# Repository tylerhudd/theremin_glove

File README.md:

# Theremin Glove
The Theremin Glove is a theremin inspired electronic instrument. Like the theremin, it is played with hand movements and gestures in the air. In electronics terms, it is a digitally controlled analog synthesizer and a wireless glove controller.
 
This project was started for the Johns Hopkins Whiting School of Engineering *Embedded Systems Lab* course in September 2019 and the working prototype should be demonstrated in December 2019. This course is an Electrical and Computer Engineerng graduate level capstone class that emulates the design process from requirement definitions to project demonstration.

I came up with the concept for this project as a way to combine areas of my engineering interests, which include:
* Analog circuit design
* Digital circuit design
* Firmware design (in this case, it's C programming for the ATMega328P)
* PCB design

## Features
* Pitch control - raising and lowering hand raises and lowers the frequency generated by the analog synthesizer
* Definable pitch range - the pitch range is set by first defining where the lowest note exists (i.e. place hand at the bottom of range) and press a button to start range recording. Then raise hand to where the highest note is and press a button to save. This is required because hand placement will be detected by an accelerometer which doesn't measure absolute height.
* Tone control - tilting hand in and out sweeps the resonant frequencies of the analog filters in the synthesizer
* Volume control - opening and closing hand raises and lowers the volume

## System
### Glove
* XBee3 wireless RF transceiver - transmits sensor data to digital analog synthesizer controller
* ATMega328P microcontroller - reads the sensor data and pushes to the XBee3 over SPI
* I2C interface to 6DoF sensor
* ADC interface to bend sensor
* USB-UART interface to ATMega328P and XBee3 for debug
* AVR SPI ISP header for ATMega328P programming
* Battery powered
* USB re-chargeable

### Digital Analog Synthesizer Controller
* XBee3 wireless RF transceiver - receives sensor data from glove
* ATMega328P microcontroller - interprets sensor data and calculates controls to analog synthesizer
* I2C interface to 4-channel DAC and IO expander
* USB-UART interface to ATMega328P and XBee3 for debug
* AVR SPI ISP header for ATMega328P programming

### Analog Synthesizer
* 4-channel DAC - provides control voltages to analog circuis
* I2C IO expander - provides a greater number of control signals
* VCO - generates square, triangle, and sine waveforms
* VCF - variable low pass, band pass, and high pass filters
* VCA - variable volume amplifier
* Analog muxes to select waveforms and filtering
* Audio output

### Power Board
* Input 12VAC (2A max)
* Ouput :
 * +3.3V DC (1.5A max) for digital circuits
 * +/-12V DC (1.5A max each) for analog circuits

### Block Diagram

## Tools Used
* Atmel Studio - for ATMega328P C firmware development and programming
* KiCAD - for schematic capture and PCB design
* LTSpice - for analog and power simulations
* PuTTY - for serial console
* Github - for configuration management and project documentation

## Resources
* http://musicfromouterspace.com/
* https://oshpark.com/

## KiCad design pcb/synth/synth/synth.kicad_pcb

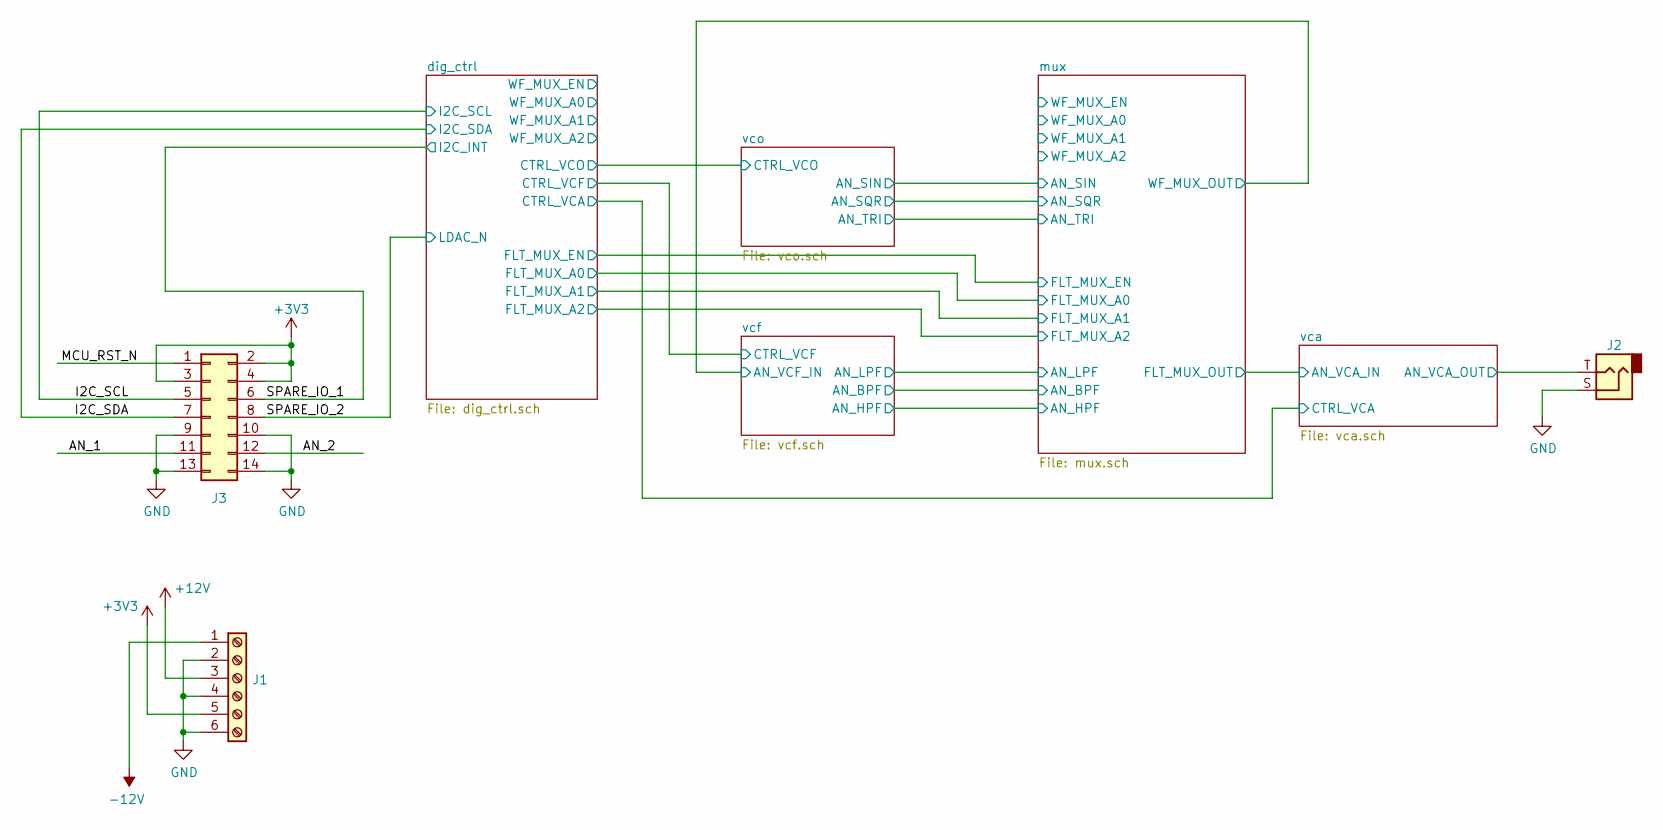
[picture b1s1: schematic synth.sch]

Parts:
J1: Screw_Terminal_01x06; TerminalBlock_bornier-6_P5.08mm
J2: AudioJack2; PinHeader_1x02_P2.54mm_Vertical
J3: Conn_02x07_Odd_Even; PinHeader_2x07_P2.54mm_Vertical

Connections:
+12V: J1.3; also elsewhere on the board
/AN_1: J3.11; also elsewhere on the board
/AN_2: J3.12; also elsewhere on the board
/I2C_SCL: J3.6; also elsewhere on the board
/I2C_SDA: J3.8; also elsewhere on the board
/SPARE_IO_1: J3.5; also elsewhere on the board
/SPARE_IO_2: J3.7; also elsewhere on the board
/vca/AN_VCA_OUT: J2.T; also elsewhere on the board
GND: J1.2, J1.4, J1.6, J2.S, J3.9, J3.10, J3.13, J3.14; also elsewhere on the board

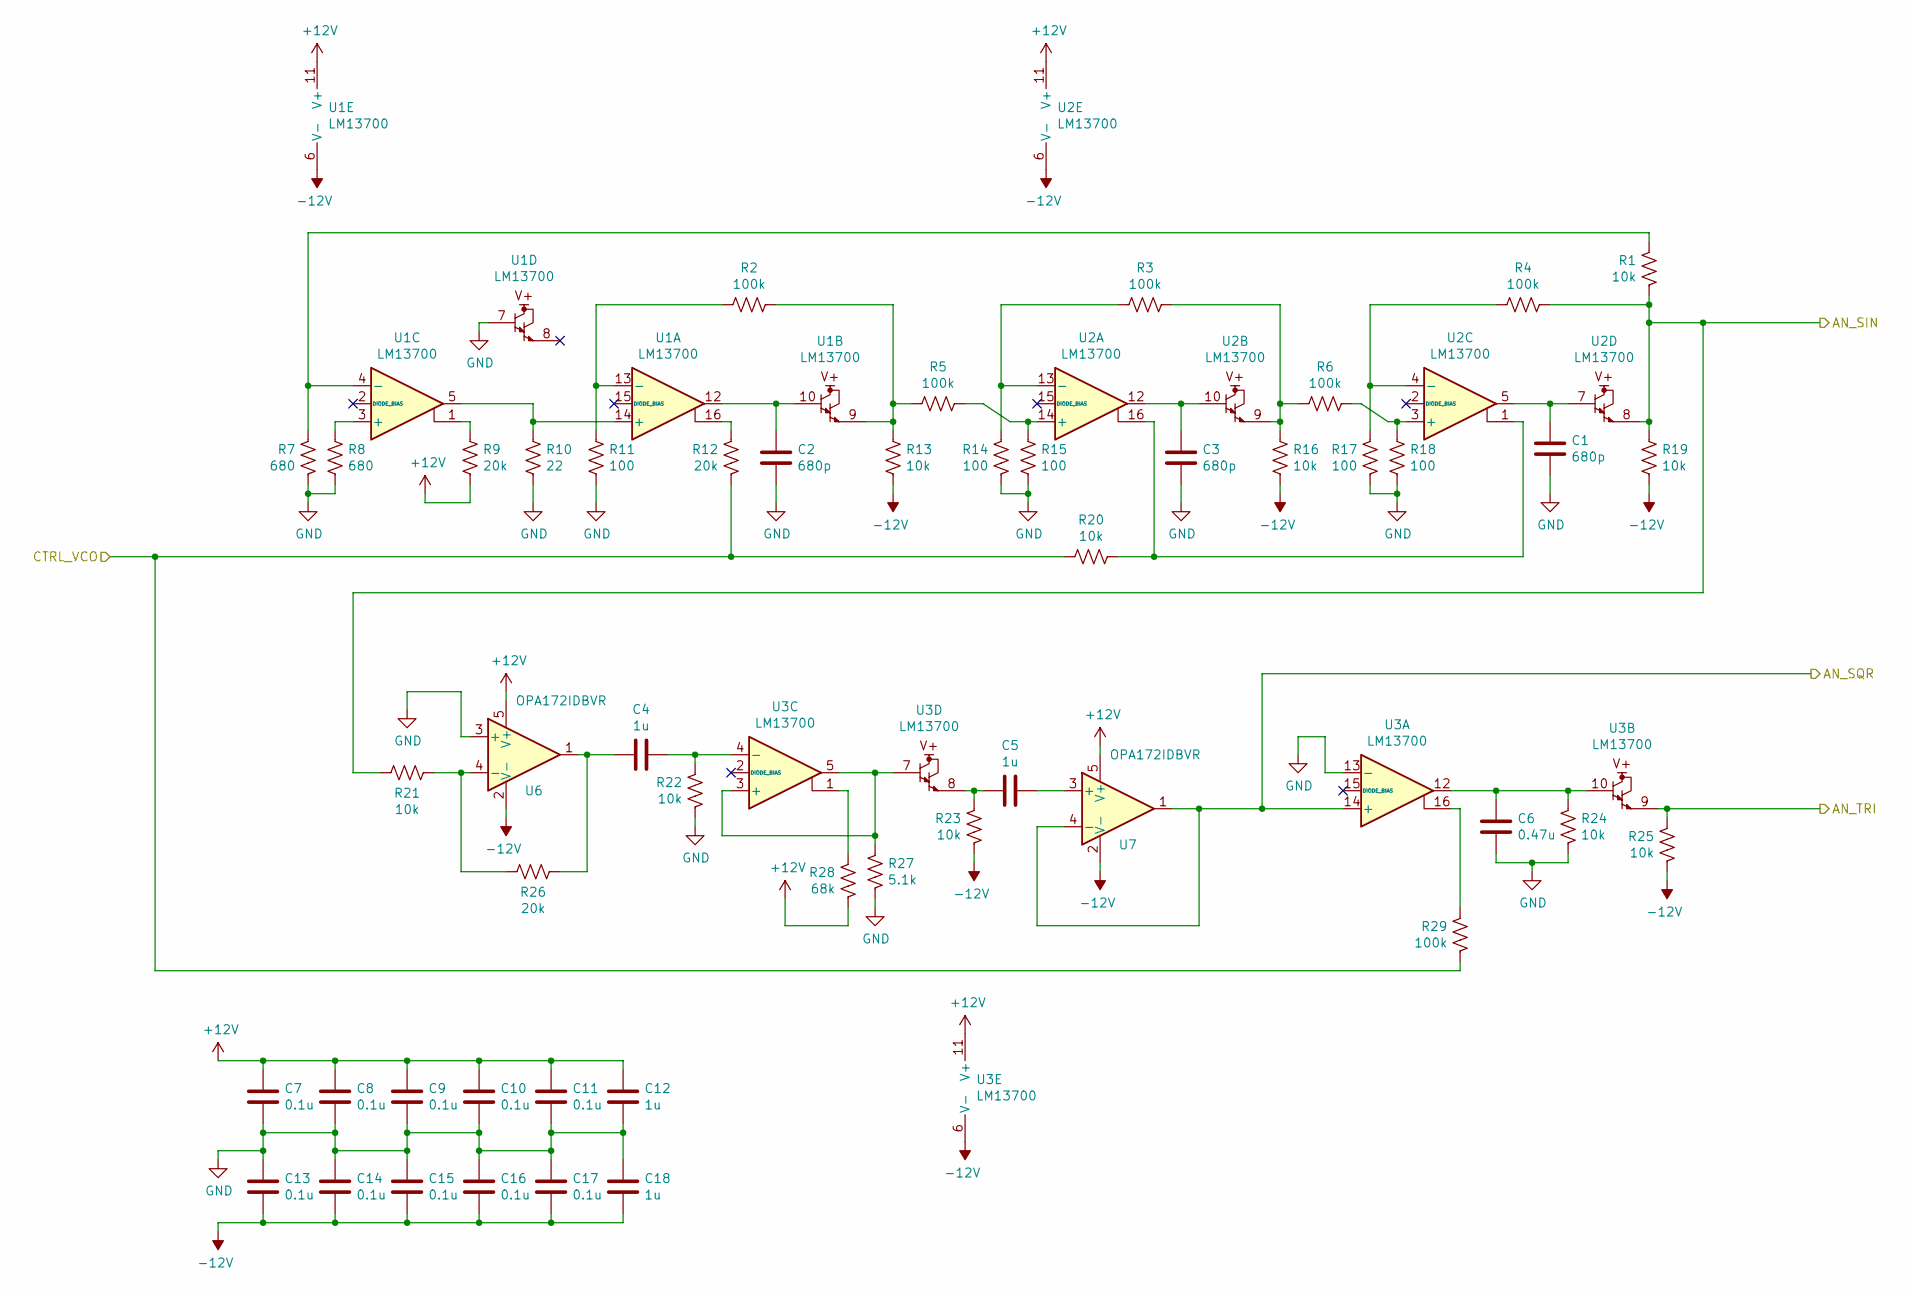
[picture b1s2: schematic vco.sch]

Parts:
C1, C2, C3: 680p; C_0603_1608Metric_Pad1.05x0.95mm_HandSolder
C4, C5, C12, C18: 1u; C_0603_1608Metric_Pad1.05x0.95mm_HandSolder
C6: 0.47u; C_0603_1608Metric_Pad1.05x0.95mm_HandSolder
C7, C8, C9, C10, C11, C13, C14, C15, C16, C17: 0.1u; C_0603_1608Metric_Pad1.05x0.95mm_HandSolder
R1, R13, R16, R19, R20, R21, R22, R23, R24, R25: 10k; R_0603_1608Metric_Pad1.05x0.95mm_HandSolder
R2, R3, R4, R5, R6, R29: 100k; R_0603_1608Metric_Pad1.05x0.95mm_HandSolder
R7, R8: 680; R_0603_1608Metric_Pad1.05x0.95mm_HandSolder
R9, R12, R26: 20k; R_0603_1608Metric_Pad1.05x0.95mm_HandSolder
R10: 22; R_0603_1608Metric_Pad1.05x0.95mm_HandSolder
R11, R14, R15, R17, R18: 100; R_0603_1608Metric_Pad1.05x0.95mm_HandSolder
R27: 5.1k; R_0603_1608Metric_Pad1.05x0.95mm_HandSolder
R28: 68k; R_0603_1608Metric_Pad1.05x0.95mm_HandSolder
U1, U2, U3: LM13700; SOIC-16_3.9x9.9mm_P1.27mm
U6, U7: OPA172IDBVR; SOT-23-5

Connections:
+12V: C7.1, C8.1, C9.1, C10.1, C11.1, C12.1, R9.1, R28.1, U1.11 (V+), U2.11 (V+), U3.11 (V+), U6.5 (V+), U7.5 (V+); also elsewhere on the board
/dig_ctrl/CTRL_VCO: R12.1, R20.2, R29.1; also elsewhere on the board
/mux/AN_SIN: R1.1, R4.1, R19.2, R21.2, U2.8; also elsewhere on the board
/mux/AN_SQR: U3.14 (+), U7.1, U7.4 (-); also elsewhere on the board
/mux/AN_TRI: R25.2, U3.9; also elsewhere on the board
GND: C1.2, C2.2, C3.2, C6.2, C7.2, C8.2, C9.2, C10.2, C11.2, C12.2, C13.1, C14.1, C15.1, C16.1, C17.1, C18.1, R7.1, R8.1, R10.1, R11.1, R14.1, R15.1, R17.1, R18.1, R22.1, R24.1, R27.1, U1.7, U3.13 (-), U6.3 (+); also elsewhere on the board
unnamed: C1.1, U2.5, U2.7
unnamed: C2.1, U1.10, U1.12
unnamed: C3.1, U2.10, U2.12
unnamed: C4.1, R26.1, U6.1
unnamed: C4.2, R22.2, U3.4 (-)
unnamed: C5.1, R23.2, U3.8
unnamed: C5.2, U7.3 (+)
unnamed: C6.1, R24.2, U3.10, U3.12
unnamed: R1.2, R7.2, U1.4 (-)
unnamed: R8.2, U1.3 (+)
unnamed: R9.2, U1.1
unnamed: R10.2, U1.5, U1.14 (+)
unnamed: R2.2, R11.2, U1.13 (-)
unnamed: R12.2, U1.16
unnamed: R2.1, R5.2, R13.2, U1.9
unnamed: R3.2, R14.2, U2.13 (-)
unnamed: R5.1, R15.2, U2.14 (+)
unnamed: R3.1, R6.2, R16.2, U2.9
unnamed: R4.2, R17.2, U2.4 (-)
unnamed: R6.1, R18.2, U2.3 (+)
unnamed: R20.1, U2.1, U2.16
unnamed: R21.1, R26.2, U6.4 (-)
unnamed: R27.2, U3.3 (+), U3.5, U3.7
unnamed: R28.2, U3.1
unnamed: R29.2, U3.16

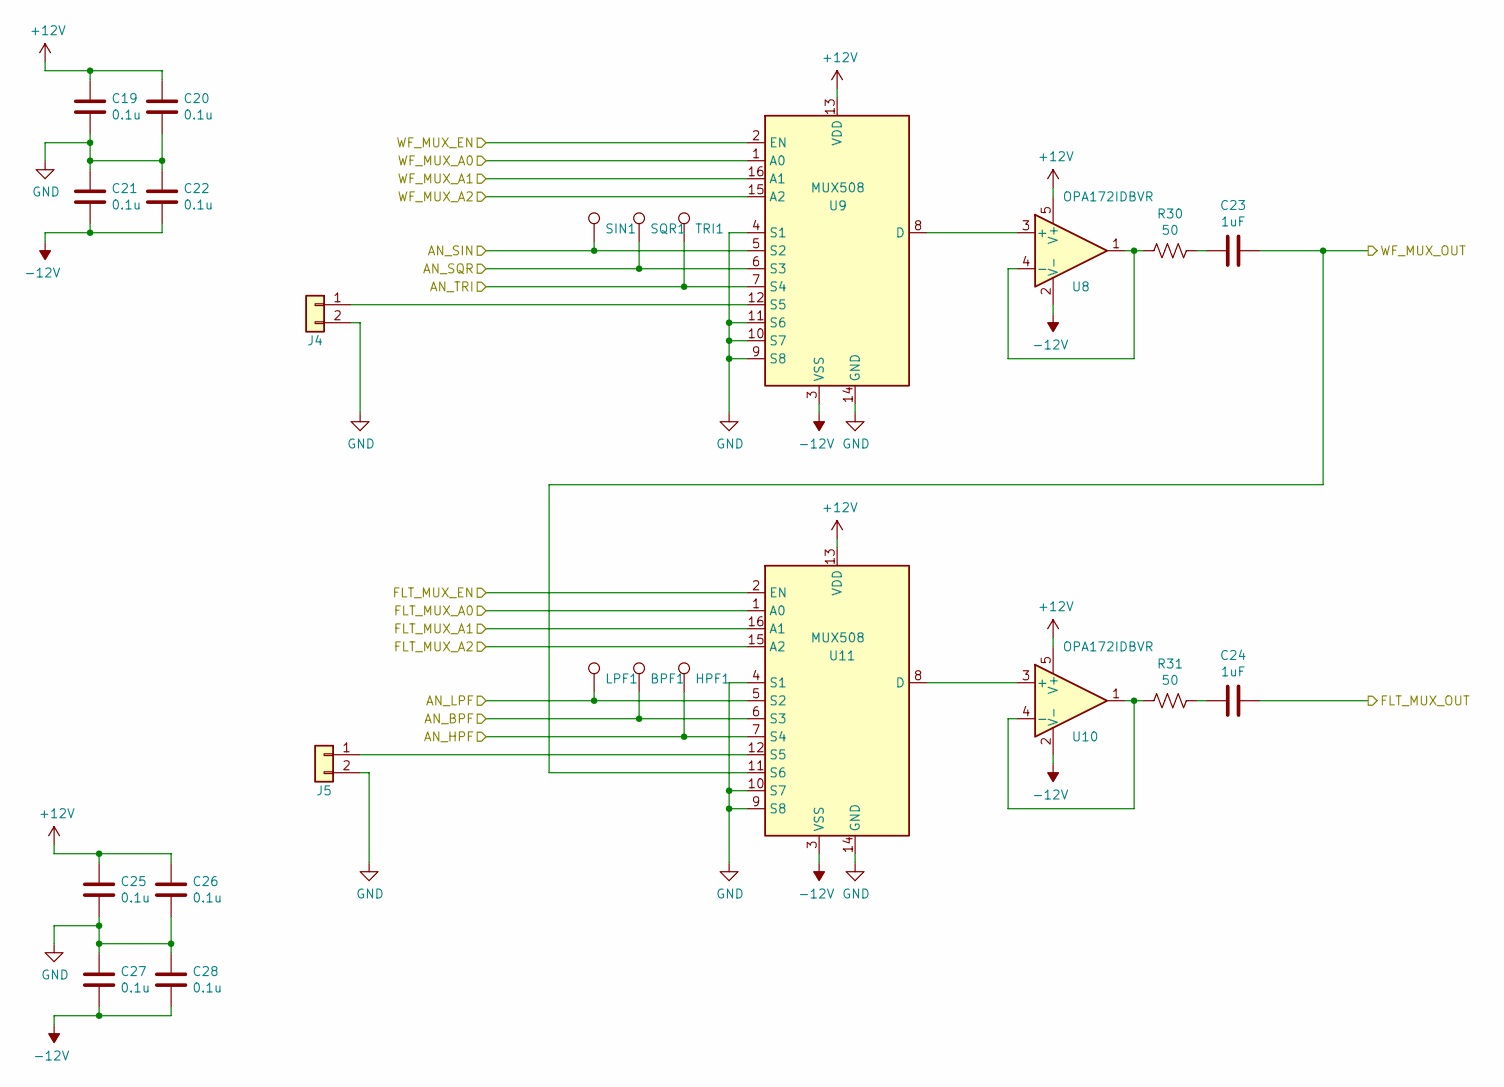
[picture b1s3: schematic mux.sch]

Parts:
BPF1: TestPoint; TestPoint_Pad_1.0x1.0mm
C19, C20, C21, C22, C25, C26, C27, C28: 0.1u; C_0603_1608Metric_Pad1.05x0.95mm_HandSolder
C23, C24: 1uF; C_0603_1608Metric_Pad1.05x0.95mm_HandSolder
HPF1: TestPoint; TestPoint_Pad_1.0x1.0mm
J4, J5: Conn_01x02; PinHeader_1x02_P2.54mm_Vertical
LPF1: TestPoint; TestPoint_Pad_1.0x1.0mm
R30, R31: 50; R_0603_1608Metric_Pad1.05x0.95mm_HandSolder
SIN1: TestPoint; TestPoint_Pad_1.0x1.0mm
SQR1: TestPoint; TestPoint_Pad_1.0x1.0mm
TRI1: TestPoint; TestPoint_Pad_1.0x1.0mm
U8, U10: OPA172IDBVR; SOT-23-5
U9, U11: MUX508; SOIC-16_3.9x9.9mm_P1.27mm

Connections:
+12V: C19.1, C20.1, C25.1, C26.1, U8.5 (V+), U9.13 (VDD), U10.5 (V+), U11.13 (VDD); also elsewhere on the board
/dig_ctrl/FLT_MUX_A0: U11.1 (A0); also elsewhere on the board
/dig_ctrl/FLT_MUX_A1: U11.16 (A1); also elsewhere on the board
/dig_ctrl/FLT_MUX_A2: U11.15 (A2); also elsewhere on the board
/dig_ctrl/FLT_MUX_EN: U11.2 (EN); also elsewhere on the board
/dig_ctrl/WF_MUX_A0: U9.1 (A0); also elsewhere on the board
/dig_ctrl/WF_MUX_A1: U9.16 (A1); also elsewhere on the board
/dig_ctrl/WF_MUX_A2: U9.15 (A2); also elsewhere on the board
/dig_ctrl/WF_MUX_EN: U9.2 (EN); also elsewhere on the board
/mux/AN_BPF: BPF1.1, U11.6 (S3); also elsewhere on the board
/mux/AN_HPF: HPF1.1, U11.7 (S4); also elsewhere on the board
/mux/AN_LPF: LPF1.1, U11.5 (S2); also elsewhere on the board
/mux/AN_SIN: SIN1.1, U9.5 (S2); also elsewhere on the board
/mux/AN_SQR: SQR1.1, U9.6 (S3); also elsewhere on the board
/mux/AN_TRI: TRI1.1, U9.7 (S4); also elsewhere on the board
/vca/AN_VCA_IN: C24.2; also elsewhere on the board
/vcf/AN_VCF_IN: C23.2, U11.11 (S6); also elsewhere on the board
GND: C19.2, C20.2, C21.1, C22.1, C25.2, C26.2, C27.1, C28.1, J4.2, J5.2, U9.4 (S1), U9.9 (S8), U9.10 (S7), U9.11 (S6), U9.14 (GND), U11.4 (S1), U11.9 (S8), U11.10 (S7), U11.14 (GND); also elsewhere on the board
unnamed: C23.1, R30.1
unnamed: C24.1, R31.1
unnamed: J4.1, U9.12 (S5)
unnamed: J5.1, U11.12 (S5)
unnamed: R30.2, U8.1, U8.4 (-)
unnamed: R31.2, U10.1, U10.4 (-)
unnamed: U8.3 (+), U9.8 (D)
unnamed: U10.3 (+), U11.8 (D)

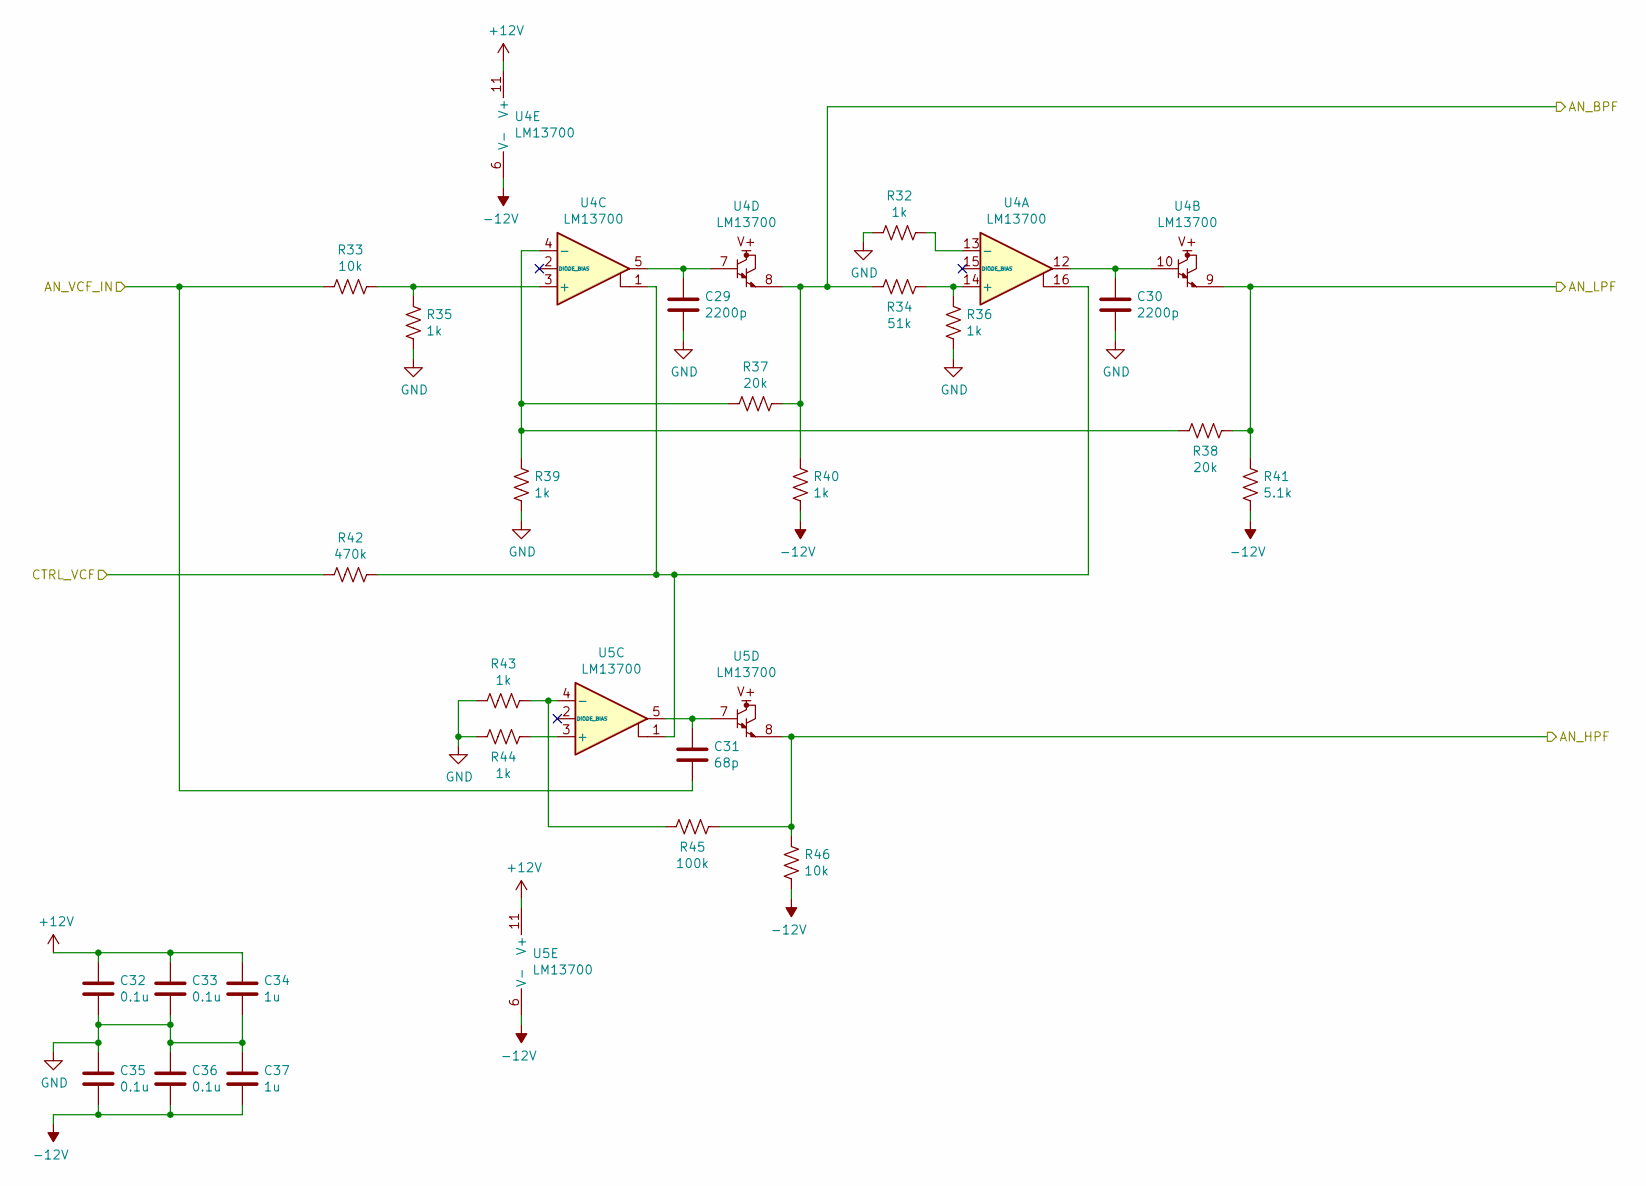
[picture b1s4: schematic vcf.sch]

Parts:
C29, C30: 2200p; C_0603_1608Metric_Pad1.05x0.95mm_HandSolder
C31: 68p; C_0603_1608Metric_Pad1.05x0.95mm_HandSolder
C32, C33, C35, C36: 0.1u; C_0603_1608Metric_Pad1.05x0.95mm_HandSolder
C34, C37: 1u; C_0603_1608Metric_Pad1.05x0.95mm_HandSolder
R32, R35, R36, R39, R40, R43, R44: 1k; R_0603_1608Metric_Pad1.05x0.95mm_HandSolder
R33, R46: 10k; R_0603_1608Metric_Pad1.05x0.95mm_HandSolder
R34: 51k; R_0603_1608Metric_Pad1.05x0.95mm_HandSolder
R37, R38: 20k; R_0603_1608Metric_Pad1.05x0.95mm_HandSolder
R41: 5.1k; R_0603_1608Metric_Pad1.05x0.95mm_HandSolder
R42: 470k; R_0603_1608Metric_Pad1.05x0.95mm_HandSolder
R45: 100k; R_0603_1608Metric_Pad1.05x0.95mm_HandSolder
U4, U5: LM13700; SOIC-16_3.9x9.9mm_P1.27mm

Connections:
+12V: C32.1, C33.1, C34.1, U4.11 (V+), U5.11 (V+); also elsewhere on the board
/dig_ctrl/CTRL_VCF: R42.2; also elsewhere on the board
/mux/AN_BPF: R34.2, R37.1, R40.1, U4.8; also elsewhere on the board
/mux/AN_HPF: R45.2, R46.1, U5.8; also elsewhere on the board
/mux/AN_LPF: R38.1, R41.1, U4.9; also elsewhere on the board
/vcf/AN_VCF_IN: C31.2, R33.2; also elsewhere on the board
GND: C29.2, C30.2, C32.2, C33.2, C34.2, C35.1, C36.1, C37.1, R32.2, R35.2, R36.2, R39.2, R43.1, R44.1; also elsewhere on the board
unnamed: C29.1, U4.5, U4.7
unnamed: C30.1, U4.10, U4.12
unnamed: C31.1, U5.5, U5.7
unnamed: R32.1, U4.13 (-)
unnamed: R33.1, R35.1, U4.3 (+)
unnamed: R34.1, R36.1, U4.14 (+)
unnamed: R37.2, R38.2, R39.1, U4.4 (-)
unnamed: R42.1, U4.1, U4.16, U5.1
unnamed: R43.2, R45.1, U5.4 (-)
unnamed: R44.2, U5.3 (+)

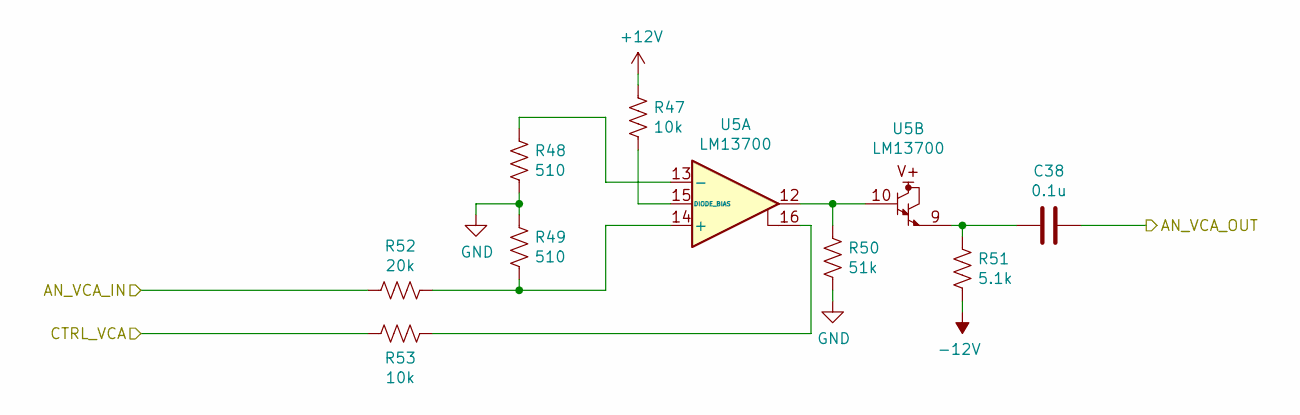
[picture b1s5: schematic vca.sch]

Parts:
C38: 0.1u; C_0603_1608Metric_Pad1.05x0.95mm_HandSolder
R47, R53: 10k; R_0603_1608Metric_Pad1.05x0.95mm_HandSolder
R48, R49: 510; R_0603_1608Metric_Pad1.05x0.95mm_HandSolder
R50: 51k; R_0603_1608Metric_Pad1.05x0.95mm_HandSolder
R51: 5.1k; R_0603_1608Metric_Pad1.05x0.95mm_HandSolder
R52: 20k; R_0603_1608Metric_Pad1.05x0.95mm_HandSolder
U5: LM13700; SOIC-16_3.9x9.9mm_P1.27mm

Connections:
+12V: R47.2; also elsewhere on the board
/dig_ctrl/CTRL_VCA: R53.2; also elsewhere on the board
/vca/AN_VCA_IN: R52.2; also elsewhere on the board
/vca/AN_VCA_OUT: C38.1; also elsewhere on the board
GND: R48.1, R49.2, R50.1; also elsewhere on the board
unnamed: C38.2, R51.2, U5.9
unnamed: R47.1, U5.15 (DIODE_BIAS)
unnamed: R48.2, U5.13 (-)
unnamed: R49.1, R52.1, U5.14 (+)
unnamed: R50.2, U5.10, U5.12
unnamed: R53.1, U5.16

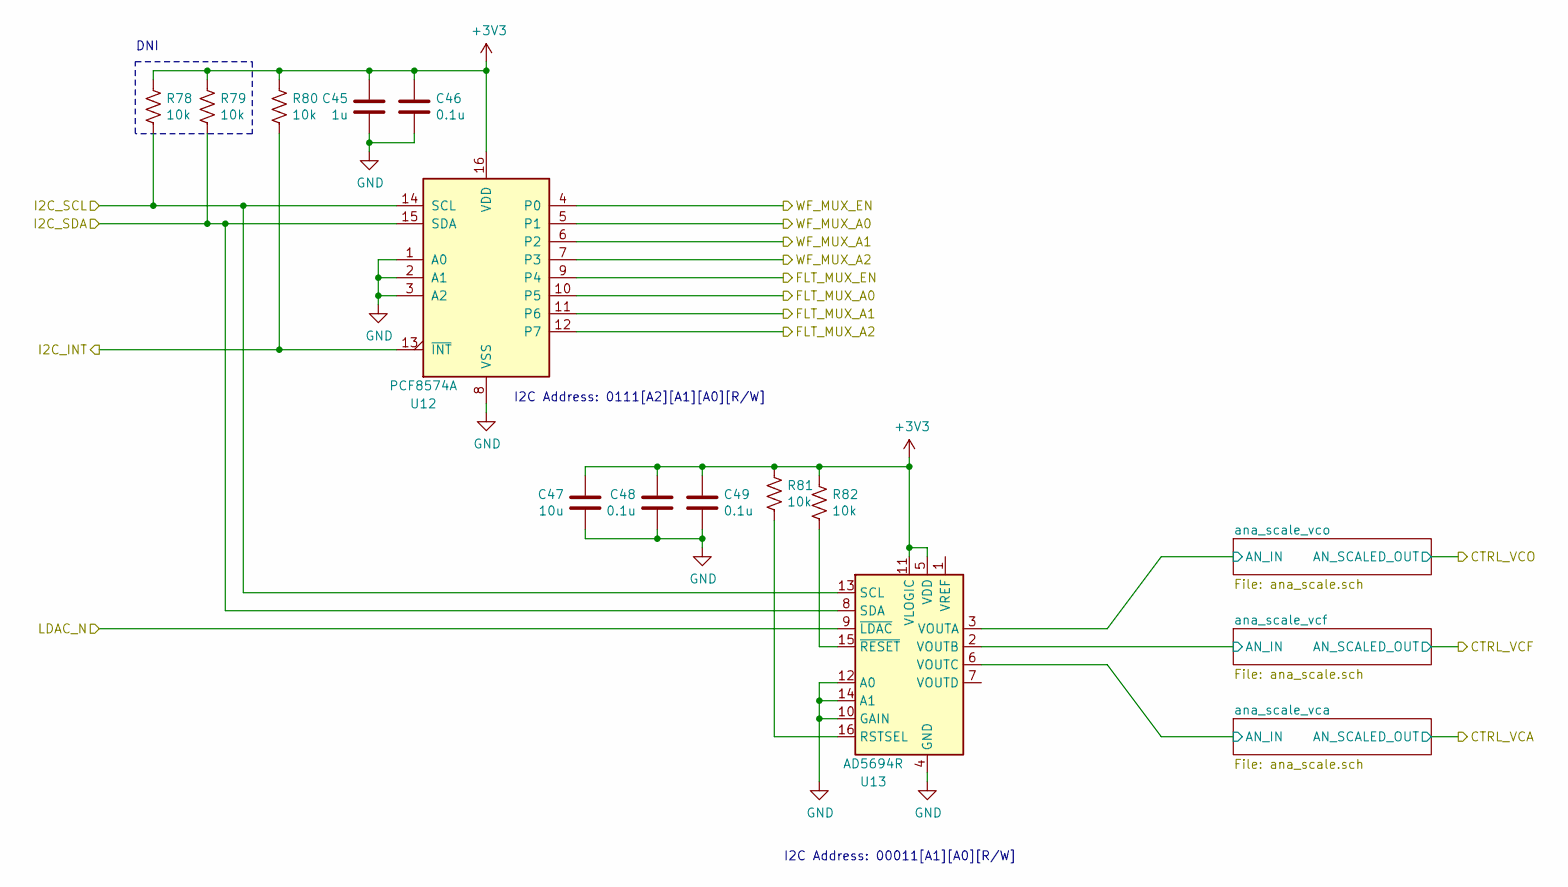
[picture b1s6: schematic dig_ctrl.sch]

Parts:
C45: 1u; C_0603_1608Metric_Pad1.05x0.95mm_HandSolder
C46, C48, C49: 0.1u; C_0603_1608Metric_Pad1.05x0.95mm_HandSolder
C47: 10u; C_0603_1608Metric_Pad1.05x0.95mm_HandSolder
R78, R79, R80, R81, R82: 10k; R_0603_1608Metric_Pad1.05x0.95mm_HandSolder
U12: PCF8574A; SOIC-16W-12_7.5x10.3mm_P1.27mm
U13: AD5694R; TSSOP-16_4.4x5mm_P0.65mm

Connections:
/I2C_SCL: R78.2, U12.14 (SCL), U13.13 (SCL); also elsewhere on the board
/I2C_SDA: R79.2, U12.15 (SDA), U13.8 (SDA); also elsewhere on the board
/SPARE_IO_1: R80.2, U12.13 (~INT~); also elsewhere on the board
/SPARE_IO_2: U13.9 (~LDAC); also elsewhere on the board
/dig_ctrl/FLT_MUX_A0: U12.10 (P5); also elsewhere on the board
/dig_ctrl/FLT_MUX_A1: U12.11 (P6); also elsewhere on the board
/dig_ctrl/FLT_MUX_A2: U12.12 (P7); also elsewhere on the board
/dig_ctrl/FLT_MUX_EN: U12.9 (P4); also elsewhere on the board
/dig_ctrl/WF_MUX_A0: U12.5 (P1); also elsewhere on the board
/dig_ctrl/WF_MUX_A1: U12.6 (P2); also elsewhere on the board
/dig_ctrl/WF_MUX_A2: U12.7 (P3); also elsewhere on the board
/dig_ctrl/WF_MUX_EN: U12.4 (P0); also elsewhere on the board
/dig_ctrl/ana_scale_vca/AN_IN: U13.6 (VOUTC); also elsewhere on the board
/dig_ctrl/ana_scale_vcf/AN_IN: U13.2 (VOUTB); also elsewhere on the board
/dig_ctrl/ana_scale_vco/AN_IN: U13.3 (VOUTA); also elsewhere on the board
GND: C45.2, C46.2, C47.2, C48.2, C49.2, U12.1 (A0), U12.2 (A1), U12.3 (A2), U12.8 (VSS), U13.4 (GND), U13.10 (GAIN), U13.12 (A0), U13.14 (A1); also elsewhere on the board
unnamed: R81.2, U13.16 (RSTSEL)
unnamed: R82.2, U13.15 (~RESET)
unnamed 101: U13.7 (VOUTD); also elsewhere on the board

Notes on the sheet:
I2C Address: 0111[A2][A1][A0][R/W]
I2C Address: 00011[A1][A0][R/W]
DNI

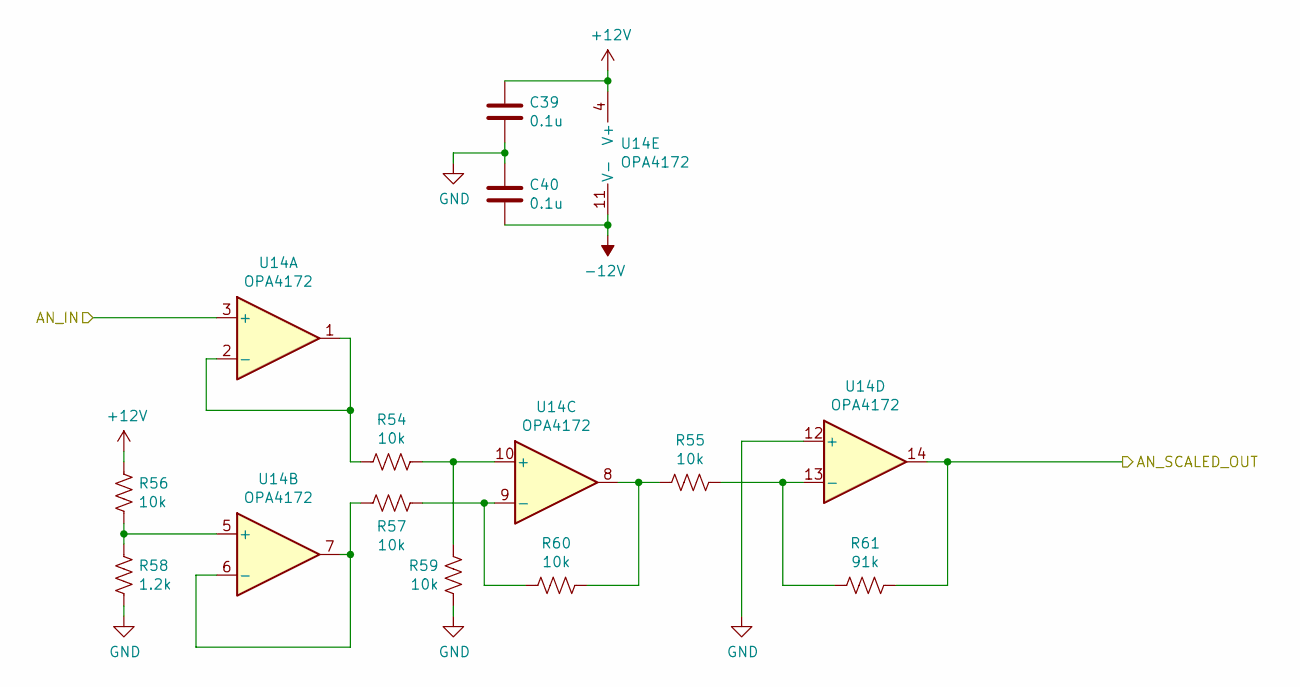
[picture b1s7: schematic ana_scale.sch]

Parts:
C39, C40: 0.1u; C_0603_1608Metric_Pad1.05x0.95mm_HandSolder
R54, R55, R56, R57, R59, R60: 10k; R_0603_1608Metric_Pad1.05x0.95mm_HandSolder
R58: 1.2k; R_0603_1608Metric_Pad1.05x0.95mm_HandSolder
R61: 91k; R_0603_1608Metric_Pad1.05x0.95mm_HandSolder
U14: OPA4172; SOIC-14_3.9x8.7mm_P1.27mm

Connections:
+12V: C39.1, R56.1, U14.4 (V+); also elsewhere on the board
/dig_ctrl/CTRL_VCO: R61.2, U14.14; also elsewhere on the board
/dig_ctrl/ana_scale_vco/AN_IN: U14.3 (+); also elsewhere on the board
GND: C39.2, C40.1, R58.2, R59.2, U14.12 (+); also elsewhere on the board
unnamed: R54.1, U14.1, U14.2 (-)
unnamed: R54.2, R59.1, U14.10 (+)
unnamed: R55.1, R60.2, U14.8
unnamed: R55.2, R61.1, U14.13 (-)
unnamed: R56.2, R58.1, U14.5 (+)
unnamed: R57.1, U14.6 (-), U14.7
unnamed: R57.2, R60.1, U14.9 (-)

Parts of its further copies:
C41, C42, C43, C44: 0.1u; C_0603_1608Metric_Pad1.05x0.95mm_HandSolder
R62, R63, R64, R65, R67, R68, R70, R71, R72, R73, R75, R76: 10k; R_0603_1608Metric_Pad1.05x0.95mm_HandSolder
R66, R74: 1.2k; R_0603_1608Metric_Pad1.05x0.95mm_HandSolder
U15, U16: OPA4172; SOIC-14_3.9x8.7mm_P1.27mm

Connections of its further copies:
+12V: C41.1, C43.1, R64.1, R72.1, U15.4 (V+), U16.4 (V+); also elsewhere on the board
/dig_ctrl/CTRL_VCA: U16.14; also elsewhere on the board
/dig_ctrl/CTRL_VCF: U15.14; also elsewhere on the board
/dig_ctrl/ana_scale_vca/AN_IN: U16.3 (+); also elsewhere on the board
/dig_ctrl/ana_scale_vcf/AN_IN: U15.3 (+); also elsewhere on the board
GND: C41.2, C42.1, C43.2, C44.1, R66.2, R67.2, R74.2, R75.2, U15.12 (+), U16.12 (+); also elsewhere on the board
unnamed: R62.1, U15.1, U15.2 (-)
unnamed: R62.2, R67.1, U15.10 (+)
unnamed: R63.1, R68.2, U15.8
unnamed 88: R63.2, U15.13 (-); also elsewhere on the board
unnamed: R64.2, R66.1, U15.5 (+)
unnamed: R65.1, U15.6 (-), U15.7
unnamed: R65.2, R68.1, U15.9 (-)
unnamed: R70.1, U16.1, U16.2 (-)
unnamed: R70.2, R75.1, U16.10 (+)
unnamed: R71.1, R76.2, U16.8
unnamed 95: R71.2, U16.13 (-); also elsewhere on the board
unnamed: R72.2, R74.1, U16.5 (+)
unnamed: R73.1, U16.6 (-), U16.7
unnamed: R73.2, R76.1, U16.9 (-)

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
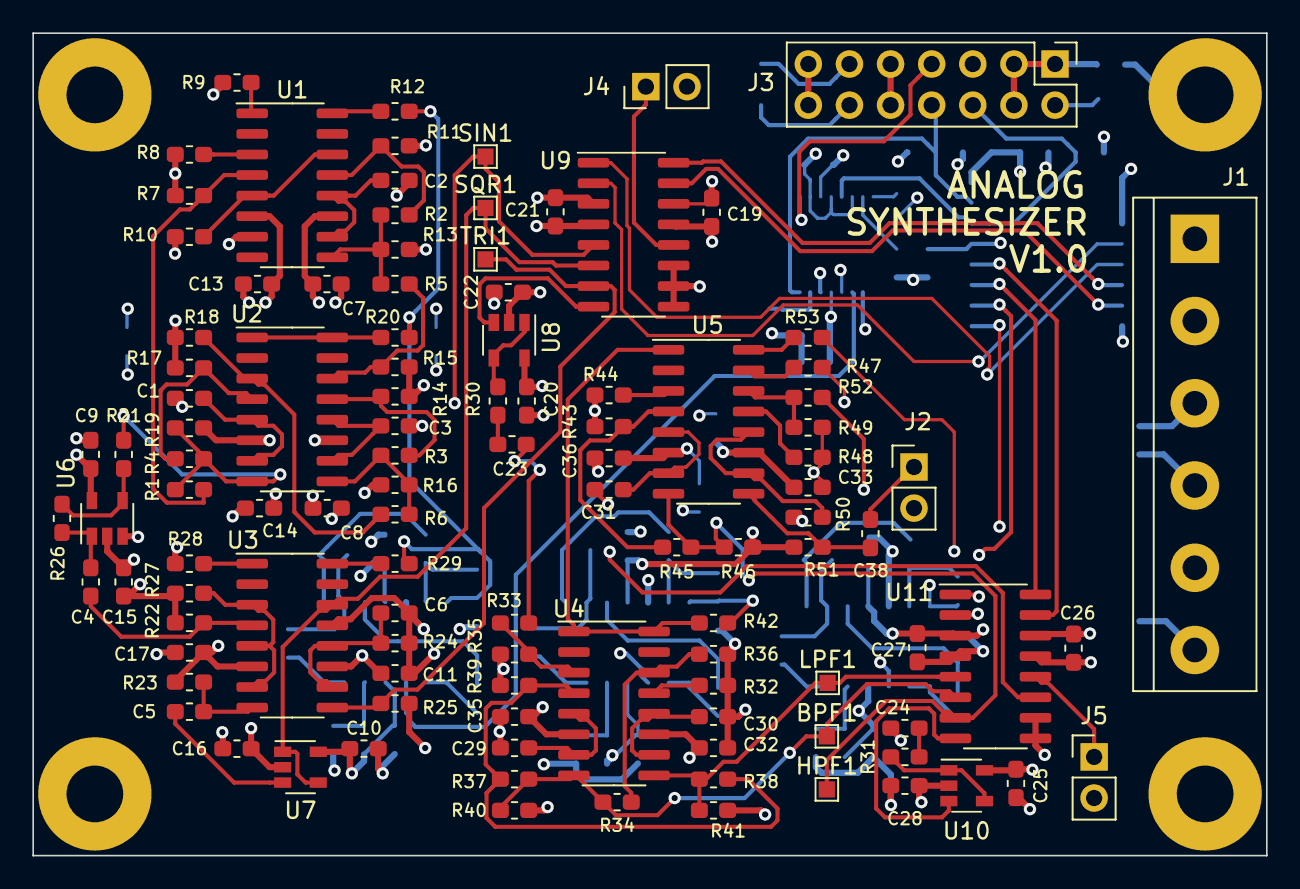
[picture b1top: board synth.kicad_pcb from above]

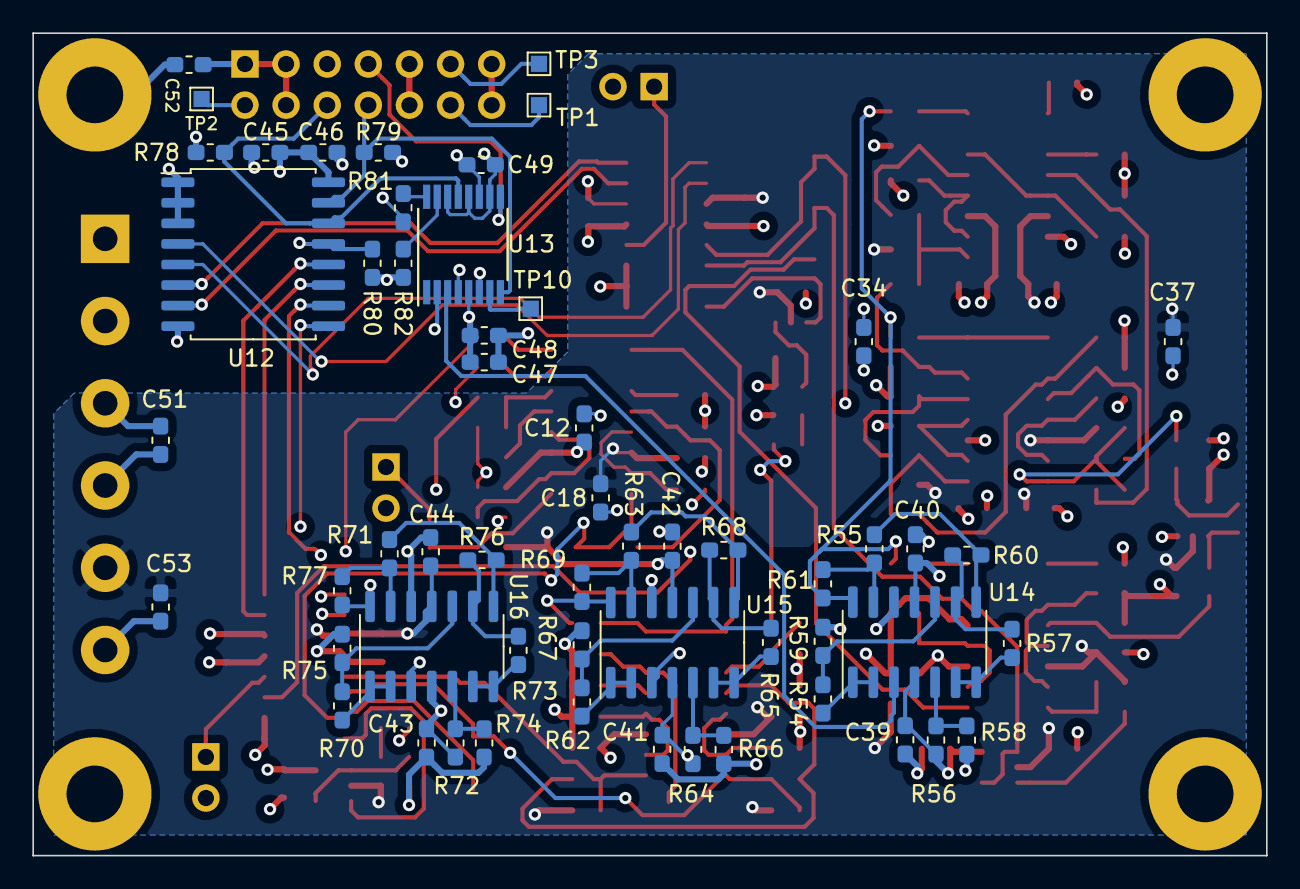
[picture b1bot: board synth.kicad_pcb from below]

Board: 4 copper layers, 76.2 x 50.8 mm, 165 parts (56 on the bottom side), 107 nets.

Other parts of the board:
C51, C52, C53: 10u; C_0603_1608Metric_Pad1.05x0.95mm_HandSolder
R69, R77: 10k; R_0603_1608Metric_Pad1.05x0.95mm_HandSolder
TP1, TP2, TP3, TP10: TestPoint; TestPoint_Pad_1.0x1.0mm

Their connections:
+12V: C51.1; also elsewhere on the board
/AN_1: TP3.1; also elsewhere on the board
/AN_2: TP1.1; also elsewhere on the board
/dig_ctrl/CTRL_VCA: R77.2; also elsewhere on the board
/dig_ctrl/CTRL_VCF: R69.2; also elsewhere on the board
GND: C51.2, C52.2, C53.1; also elsewhere on the board
unnamed 88: R69.1; also elsewhere on the board
unnamed 95: R77.1; also elsewhere on the board
unnamed 101: TP10.1; also elsewhere on the board

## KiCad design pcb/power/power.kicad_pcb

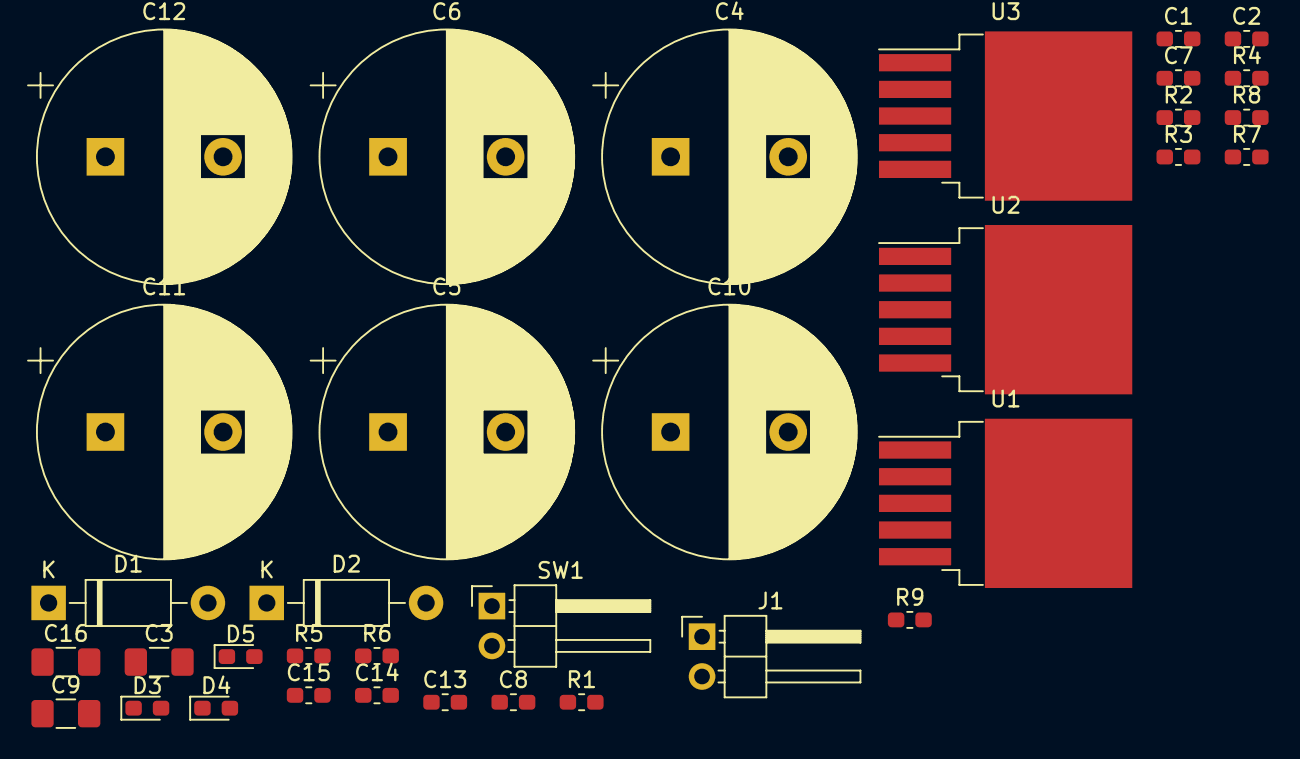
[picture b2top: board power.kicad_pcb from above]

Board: 2 copper layers, 35 parts (0 on the bottom side), 14 nets, no tracks yet.

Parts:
C1, C2, C7, C8, C13, C15: 1uF; C_0603_1608Metric_Pad1.05x0.95mm_HandSolder
C3, C9, C16: 10uF; C_1206_3216Metric_Pad1.42x1.75mm_HandSolder
C4, C5, C6, C10, C11, C12: 3300uF; CP_Radial_D16.0mm_P7.50mm
C14: 10nF; C_0603_1608Metric_Pad1.05x0.95mm_HandSolder
D1, D2: 1N4004; D_DO-41_SOD81_P10.16mm_Horizontal
D3, D4, D5: LED; LED_0603_1608Metric_Pad1.05x0.95mm_HandSolder
J1: Barrel_Jack; PinHeader_1x02_P2.54mm_Horizontal
R1: 330k; R_0603_1608Metric_Pad1.05x0.95mm_HandSolder
R2, R4, R6: 12.1k; R_0603_1608Metric_Pad1.05x0.95mm_HandSolder
R3: 1.2Meg; R_0603_1608Metric_Pad1.05x0.95mm_HandSolder
R5: 107K; R_0603_1608Metric_Pad1.05x0.95mm_HandSolder
R7: 330; R_0603_1608Metric_Pad1.05x0.95mm_HandSolder
R8, R9: 1k; R_0603_1608Metric_Pad1.05x0.95mm_HandSolder
SW1: SW_SPST; PinHeader_1x02_P2.54mm_Horizontal
U1, U2: LT3080xQ; TO-263-5_TabPin3
U3: LT3015Q; TO-263-5_TabPin3

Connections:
+3V3: C2.1, C3.1, D3.2, R2.1, U1.3
+12V: C8.1, C9.1, D4.2, R4.1, U2.3
-12V: C14.1, C15.1, C16.1, D5.1, R5.1, U3.5
/12VAC: J1.1, SW1.1
/12VAC_SW: D1.2, D2.1, SW1.2
/N12VAC_RECT: C10.1, C11.1, C12.1, C13.1, D2.2, U3.1, U3.3
/P12VAC_RECT: C1.1, C4.1, C5.1, C6.1, C7.1, D1.1, U1.4, U1.5, U2.4, U2.5
GND: C1.2, C2.2, C3.2, C4.2, C5.2, C6.2, C7.2, C8.2, C9.2, C10.2, C11.2, C12.2, C13.2, C15.2, C16.2, J1.2, R1.2, R2.2, R3.2, R4.2, R6.2, R7.1, R8.1, R9.1, U3.2
unnamed: C14.2, R5.2, R6.1, U3.4
unnamed: D3.1, R7.2
unnamed: D4.1, R8.2
unnamed: D5.2, R9.2
unnamed: R1.1, U1.2
unnamed: R3.1, U2.2
